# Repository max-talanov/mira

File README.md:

# MIRA

## Интерактивный атлас архитектуры 4.3

**[Скачать атлас ZIP](https://github.com/max-talanov/mira/raw/refs/heads/main/docs/architecture-atlas/MIRA_Architecture_Atlas_4.3.zip)** · **[Инструкция по запуску](docs/architecture-atlas/README.md)**

Скачайте и полностью распакуйте архив, затем откройте `MIRA_Architecture_Atlas/index.html` в Firefox или Chrome. Атлас работает локально: установка, сервер, интернет и KiCad для просмотра не нужны. Кнопка **«Презентация»** запускает обзор архитектуры; `guide.html` содержит текст для выступления.

Атлас 4.3 — отдельный демонстрационный снимок схем, подготовленный 22 октября 2026 года. Он не включает последующие исправления плат. Актуальные инженерные исходники находятся в [`hardware/`](hardware/).

## Обновления схем

**MIRA.06, 30 октября 2026:** [компоненты, разъёмы и сборка](docs/pcb-preparation/components-assembly/README.md). Уточнены 112 записей компонентов; исправлены SMT-footprint J100 и отверстия J600. BOM: 2148 обозначений / 322 группы; закупочные статусы и условия монтажа BGA/0201 записаны. Схемные соединения сохранены. Чертёж и открывание сокета, полный OPN входного клеммника, закупка, допуски и нагрузка разъёмов, подтверждение сборщика остаются открытыми; разрешения на производство нет.

**MIRA.05, 30 октября 2026:** [требования аналоговой части и исправления схемы](docs/pcb-preparation/analog-requirements/README.md). U2109 заменён на INA149AIDR с новой распиновкой; потолок команды снижен до 10,05 В, порог готовности P15 повышен до 13,22 В. Сохранены исправления пары CV 100/101 кОм и восьми записей BOM из промежуточного обновления; итоговая дельта — 12 компонентов. Заданы предварительные диапазоны READ/SET/RESET/FORMING, ток, нагрузка, одновременность и время; свойства реальной матрицы оставлены неизвестными. ERC 0 ошибок / 0 предупреждений на обеих платах. Пиковый ток, устойчивость, точность и время импульсов требуют отдельной проверки; прошивка и PCB не изменены.

**Решение от 30.10.2026: проверка MIG/Vivado отложена по согласованию с пользователем. Вернуться к ней перед трассировкой FPGA ↔ DDR3L на плате Control и до окончательной фиксации распиновки FPGA. По решению пользователя текущая карточка MIRA.04 закрывается как завершённый схемный этап; проверка MIG остаётся незавершённым условием перед трассировкой. Остальные проверки схемы, проектирование Power и независимые участки Control можно продолжать.**

**MIRA.04, 30 октября 2026:** [проверка цифровых интерфейсов](docs/pcb-preparation/digital-interfaces/README.md). SPI SCK перенесён AB12 → Y11; FMC/AF и 164 FPGA-порта сверены, ERC 0/0. MIG/Vivado ещё не запускались; кандидатные XDC и процедура запуска находятся в `fpga/digital-interfaces/`. Закрытие текущей карточки не означает выполнения проверки MIG; её нужно завершить до трассировки DDR3L.

**Предыдущий этап v6, 30 октября 2026:** [исправления сигналов при отключённом питании](docs/pcb-preparation/signal-remediation/README.md). Power — 61 лист / Control — 43; ERC 0/0. Закрытие — по схеме в указанных условиях; испытания платы и PCB открыты. AON: суммарный добавочный резерв 112 mA и 2.8 µF к бюджету 28 октября. Данные прежних этапов ниже сохранены как история.

**MIRA is a research platform under development for experiments with memristor arrays and neuromorphic computing.**

The project aims to bring array control, an analog front end, digital processing, and software tools into a single system. It is intended for studying memristor readout and programming, vector–matrix multiplication (VMM), and spiking neuron models.

## Current status

The current **MIRA.05 analog requirements** revision defines a provisional operating envelope and repairs the anti-windup amplifier, command ceiling and P15 qualifier. See the [analog report](docs/pcb-preparation/analog-requirements/README.md). Native ERC and historical regressions pass; matrix-specific limits, loop stability and transient peak-current qualification remain open.

The previous **2026-10-30 v6 signal remediation** adds hardware protection for PM, DAC, ADC/FDA and comparator inputs; replaces 33 analog switch ICs with fail-safe-input parts; isolates 10 VIN-relative enable paths; and qualifies USB and FPGA AUX/IO supplies. See the [current review and operating conditions](docs/pcb-preparation/signal-remediation/README.md). There are 271 new components and 40 changed legacy values. Native KiCad ERC reports zero errors and warnings. The checklist can be closed as a schematic review within those conditions. PCB, firmware and prototype qualification remain open. The [v5 receiver-only report](docs/pcb-preparation/unpowered-signals/README.md) is historical.

The preceding [fault hardware repair](docs/pcb-preparation/fault-review/README.md) adds a 170–230 ms application heartbeat watchdog, first-edge readiness and direct host reset on watchdog expiry. LINK_READY_H feeds the matrix interlock and PM PC15. The 14 added components are checked by native netlist and ideal timing/latch tests; firmware and prototype validation remain open.

The **2026-10-29** update adds [AON startup gating and full-swing VTT enable](docs/pcb-preparation/startup/README.md), plus [PM clear feedback and the 15-rail sequencing contract](docs/pcb-preparation/sequencing/README.md). The PM firmware must read GLOBAL_CLEAR_N on PC14 before arming, then confirm GLOBAL_PWR_PERMIT. Firmware implementation and prototype fault/ramp tests remain open.

**RevA** is currently in development. The repository contains two independent KiCad projects with local libraries: **MIRA_Control (43 active schematic pages)** and **MIRA_Power (61 active schematic pages)**.

Control includes MCU, FPGA, communications, matrix, analog, and protection circuits. Both projects are undergoing review before PCB placement and routing.

The [high-load schematic candidate](docs/pcb-preparation/high-load/README.md) dated **2026-10-28** adds a supplemental CORE connector and positive remote sense, replaces N15 with a TEN 30-2413WIN module, and coordinates N15 overcurrent and input overvoltage thresholds. The candidate input range is **18–30 V DC**, nominal 24 V. The provisional targets are CORE 5.2 A and N15 0.468 A; hardware capacity has not been validated.

The [distributed power interface](docs/pcb-preparation/distributed-power/README.md) replaces the central 64-contact connector with **seven local power entries and one separate supervision interface**. The zones are FPGA, DDR, MCU, USB, Ethernet, DAC/matrix and ADC/AFE. Eight Samtec SSW/HTSW pairs have assigned parts, local footprints and nominal 3D envelope models. The proposed stack has Power below Control and a 12 mm facing-surface gap; final placement coordinates and routing remain to be defined.

All 118 mating contacts were checked. The 6686-entry connector regression baseline from `c72edb2` remains matched after explicitly mapping back the documented startup, PC14 feedback, fault hardware the three v5 receive-path changes, and the explicit v6 signal-remediation delta; unrelated source/load circuits and positive CORE sense are preserved. The new pinout requires updating both projects together. The [earlier connector/ERC report](docs/pcb-preparation/connectors-erc/README.md) is retained as history.

KiCad CLI 10.0.8 reports **0 errors / 0 warnings / 0 exclusions for both projects**. Negative analog supply pins are now named VSS_NEG, with their power-input types and nets preserved; 32 old exclusions were removed. Two existing style checks remain ignored (`four_way_junction`, `single_global_label`); footprint-filter and simulation-model checks were re-enabled. PCB layout, mechanical and thermal qualification, feedback stability, startup and analog noise remain open. The [task 1/2 status and remaining questions](docs/pcb-preparation/README.md), [current ERC review](docs/pcb-preparation/erc/README.md) and [updated power budget](docs/pcb-preparation/power-budget/README.md) describe the current candidate. Original reports and calculations remain available as history. The budget applies a 30% margin to provisional peak loads and explicitly leaves N15 startup and shared-rail current distribution unresolved.

Schematics in this repository do not imply that the corresponding circuits have been built or validated in hardware.

## Repository contents

| Project | Current contents | Open in KiCad |
| --- | --- | --- |
| [MIRA_Power](hardware/MIRA_Power) | Power schematics, hierarchy, and local libraries | `hardware/MIRA_Power/MIRA_Power.kicad_pro` |
| [MIRA_Control](hardware/MIRA_Control) | 43-page schematic hierarchy, an empty PCB, and local symbol, footprint, and 3D libraries | `hardware/MIRA_Control/MIRA_Control.kicad_pro` |

Each project has its own library tables and project-relative library paths. Keep its complete folder together.

The power project includes:

| File or directory | Purpose |
| --- | --- |
| `MIRA_Power.kicad_pro` | KiCad project file |
| `MIRA_Power.kicad_sch` | Top-level schematic and hierarchy navigation |
| `POWER_SYSTEM.kicad_sch` | Power system overview |
| `POWER_INPUT.kicad_sch` | Power input and primary protection |
| `PRIMARY_POWER.kicad_sch` | Primary power converters |
| `SECONDARY_POWER.kicad_sch` | Secondary power converters |
| `PROGRAM_SWITCHES.kicad_sch` | Programming voltage switching |
| `POWER_CONTROL.kicad_sch` | Power control and protection interlocks |
| `POWER_MONITOR.kicad_sch` | Voltage and current monitoring |
| `libraries/` | Local symbol, footprint, and 3D model libraries |

The power system is designed around an external **24 V DC supply**. It provides digital and analog power rails, controlled startup, rail monitoring, and fault shutdown.

## Planned architecture

- **Memristor array and analog front end:** readout, programming, and VMM operations.
- **FPGA:** array timing control and high-speed data transfer.
- **STM32:** neuron model computation and control tasks.
- **USB 3.0 and Ethernet:** communication with a host computer.
- **Mira Studio:** a desktop application for configuring experiments, controlling the device, visualizing data, and saving results.

These blocks describe the planned development direction. Their implementation status is reflected in the current project files.

## Opening the projects

1. Clone the repository:

   ```bash
   git clone https://github.com/max-talanov/mira.git
   ```

2. Open the required `.kicad_pro` file from the table above. On Linux:

   ```bash
   cd mira
   kicad hardware/MIRA_Power/MIRA_Power.kicad_pro
   # Or open the control project:
   kicad hardware/MIRA_Control/MIRA_Control.kicad_pro
   ```

3. In both projects, use the schematic hierarchy to navigate between blocks. Open the root schematic through the project manager so the project-relative libraries are available.

Keep the directory structure intact. The `sym-lib-table` and `fp-lib-table` files are stored alongside the project and reference its local libraries.

## Versioning

**RevA** identifies the hardware revision. Git tags such as `v0.1.0` mark development milestones in the repository history.

| Tag | Milestone |
| --- | --- |
| `v0.1.0` | Initial KiCad project and local library import |
| `v0.2.0` | Separate Power and empty Control projects, with updated repository documentation |

Use commits for routine edits and annotated tags for milestones. Keep published tags on their original commits. A new repository tag does not change the hardware revision or indicate completed hardware validation.

See [CHANGELOG.md](CHANGELOG.md), the [commit history](https://github.com/max-talanov/mira/commits/main), and the [tag list](https://github.com/max-talanov/mira/tags).

## Licenses and attribution

See [LICENSE](LICENSE) and the third-party library and model notices included under each project's `libraries/` directory. Keep those notices with the corresponding assets.

## Next steps

- Establish the FPGA/matrix maximum operating scenario and recalculate the full power budget for the new N15 module.
- Co-design both PCB floorplans around the eight connector pairs; place regulators and local returns near their assigned load zones and qualify the proposed 12 mm mechanical stack.
- Validate CORE remote-sense stability, N15 startup/protection/noise and input surge response.
- Complete the remaining domain sequencing, reset/STOP and VTT/DDR_VREF reviews listed in the [candidate report](docs/pcb-preparation/high-load/README.md). The VSS ERC-exclusion review is resolved in the connector/ERC update.
- Prepare and review component placement and PCB routing before hardware validation.

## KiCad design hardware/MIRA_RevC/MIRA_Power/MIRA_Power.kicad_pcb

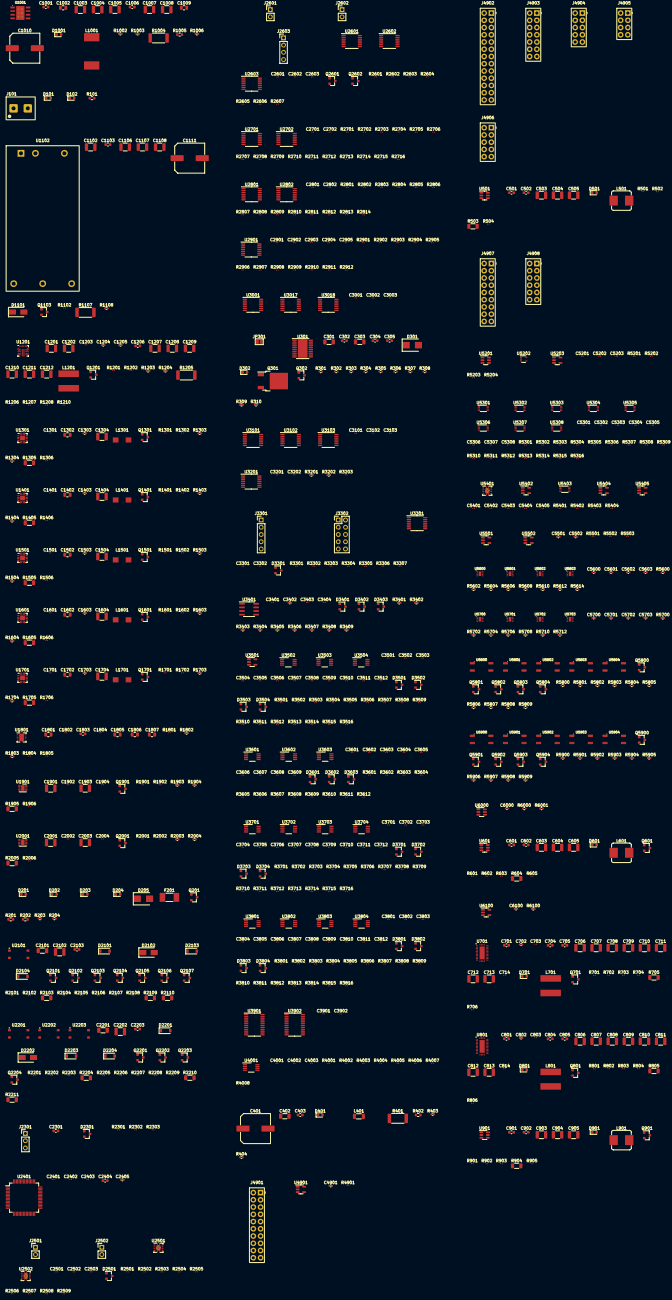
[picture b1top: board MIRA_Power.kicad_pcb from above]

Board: 4 copper layers, 793 parts (0 on the bottom side), 403 nets, no tracks yet.

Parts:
C301, C303, C402: 1u; C_1206_3216Metric
C302, C304, C305, C403, C501, C502, C601, C602, C705, C805, C901, C902, C1001, C1006, C1103, C2103, C2203, C2301: 100n; C_0603_1608Metric
C401, C1010, C1111: 100u; C_Elec_10x10.2
C503, C603, C706, C707, C806, C807, C903, C1003, C1008, C1102, C2102, C2202: 4.7u; C_1210_3225Metric
C504, C505, C604, C605, C708, C709, C710, C711, C712, C713, C808, C809, C810, C811, C812, C813, C904, C905, C1201, C1202, C1207, C1208, C1209, C1210, C1211, C1212, C1304, C1404, C1504, C1604, C1704, C1901, C1903, C2001, C2003: 47u; C_1210_3225Metric
C701, C801: 2.2u; C_0603_1608Metric
C702, C802, C2405: 1u; C_0402_1005Metric
C703, C803, C1203: 22n; C_0201_Murata_GRM03_Gap0.25
C704, C804: 470n; C_0603_1608Metric
C714, C814: 150p; C_0201_Murata_GRM03_Gap0.25
C1002: 220n; C_0805_2012Metric
C1004, C1005, C1007: 10u; C_1210_3225Metric
C1009: 1u; C_0805_2012Metric
C1106, C1107, C1108: 22u; C_1210_3225Metric
C1204, C1205, C1303, C1403, C1503, C1603, C1703, C3402, C4901, C5501, C5502, C5600, C5601, C5602, C5603, C5700, C5701, C5702, C5703, C6000, C6100: 100n; C_0402_1005Metric
C1206, C1803, C2404: 4.7u; C_0603_1608Metric
C1301, C1401, C1501, C1601, C1701, C1904, C2004, C2502, C2901, C2902, C2903, C2904, C3201, C3301, C3501, C3503, C3504, C3506, C3507, C3509, C3510, C3512, C3601, C3603, C3604, C3606, C3607, C3609, C3701, C3703, C3704, C3706, C3707, C3709, C3710, C3712, C3801, C3802, C3805, C3806, C3807, C3808, C3811, C3812: 10n; C_0201_Murata_GRM03_Gap0.25
C1302, C1402, C1502, C1602, C1702, C1801, C1805, C1806, C1807: 10u; C_0805_2012Metric
C1802, C1804, C1902, C2002, C2401, C2402, C2403, C2501, C2503, C2601, C2602, C2603, C2701, C2702, C2801, C2802, C2905, C3001, C3002, C3003, C3101, C3102, C3103, C3202, C3302, C3401, C3403, C3404, C3502, C3505, C3508, C3511, C3602, C3605, C3608, C3702, C3705, C3708, C3711, C3803, C3804, C3809, C3810, C3901, C3902, C4001, C5201, C5202, C5203, C5301, C5302, C5303, C5304, C5305, C5306, C5307, C5308, C5401, C5402, C5403, C5404, C5405: 100n; C_0201_Murata_GRM03_Gap0.25
C2101, C2201: 47n; C_1206_3216Metric
C4002, C4003: 1n; C_0201_Murata_GRM03_Gap0.25
D101, D202, D302: Red LED; LED_0603_1608Metric
D102, D204, D401, D501, D601, D701, D801, D901, D1001: Green LED; LED_0603_1608Metric
D201, D203: CD0603-B0240R; D_0603_1608Metric
D205: SMBJ36CA; D_SMB
D301: STPS3H100U; D_SMB
D1101: SS14-13-F; D_SMA
D2101, D2103, D2104, D2201, D2203, D2204: 10V G-S CLAMP; D_SOD-123
D2102, D2202: SS14 OUTPUT CLAMP; D_SMA
D2301: BAT54S ADC CLAMP; SOT-23
D2501: BAT54A; SOT-23
D3301, D3401, D3402, D3403, D3501, D3502, D3503, D3504, D3601, D3602, D3603, D3701, D3702, D3703, D3704, D3801, D3802, D3803, D3804: BAT54S; SOT-23
F201: 5A / 125V; Fuse_Littelfuse_0451_2410_Mfr
J101: DG126-5.0-02P-14; TerminalBlock_Degson_DG126-5.0-02P-14_1x02_P5.00mm
J2301: PROGRAM +/-15V; PinHeader_1x03_P2.54mm_Vertical
J2501: PM MANUAL RESET CONTACT; PinHeader_1x02_P2.54mm_Vertical
J2502: HOST MANUAL RESET CONTACT; PinHeader_1x02_P2.54mm_Vertical
J2601: GLOBAL STOP - CLOSE TO TRIP; PinHeader_1x02_P2.54mm_Vertical
J2602: MATRIX STOP - CLOSE TO TRIP; PinHeader_1x02_P2.54mm_Vertical
J2603: MATRIX HARDWARE INTERLOCK - AON LOGIC; PinHeader_1x04_P2.54mm_Vertical
J3301: PM SWD - VTREF ONLY; PinHeader_1x05_P2.54mm_Vertical
J3302: MAIN CONTROLLER UART / WATCHDOG / STATUS; PinHeader_2x05_P2.54mm_Vertical
J4901: SSW-110-01-S-D; Samtec_SSW-110-01-S-D_2x10_P2.54mm_Vertical
J4902: SSW-113-01-S-D; Samtec_SSW-113-01-S-D_2x13_P2.54mm_Vertical
J4903: SSW-107-01-S-D; Samtec_SSW-107-01-S-D_2x07_P2.54mm_Vertical
J4904, J4906: SSW-105-01-S-D; Samtec_SSW-105-01-S-D_2x05_P2.54mm_Vertical
J4905: SSW-104-01-S-D; Samtec_SSW-104-01-S-D_2x04_P2.54mm_Vertical
J4907: SSW-109-01-S-D; Samtec_SSW-109-01-S-D_2x09_P2.54mm_Vertical
J4908: SSW-106-01-S-D; Samtec_SSW-106-01-S-D_2x06_P2.54mm_Vertical
JP301: SolderJumper_2_Open; SolderJumper-2_P1.3mm_Open_Pad1.0x1.5mm
L401: 120R @ 100MHz / 6A; L_1206_3216Metric
L501, L601, L901: 33uH; L_Bourns_SRP7028A_7.3x6.6mm
L701, L801: 6.8uH; L_Bourns_SRP7030CA_7.8x7.6mm
L1001: 47u; L_Wurth_7447709101_12x12mm
L1201: 1u; L_Bourns_SRP7030CA_7.8x7.6mm
L1301, L1401, L1501, L1601, L1701: 2.2u; L_Bourns_SRP5030TA_5.7x5.2mm
Q201, Q302, Q601, Q701, Q801, Q901, Q1103, Q1201, Q1301, Q1401, Q1501, Q1601, Q1701, Q1901, Q2001, Q2601, Q2602: BSS138N; SOT-23
Q301: IRFR3410; TO-252-2
Q2101, Q2104, Q2106, Q2107, Q2201, Q2202, Q2203, Q5800, Q5801, Q5802, Q5803, Q5804, Q5900, Q5901, Q5902, Q5903, Q5904: AO3400A; SOT-23
Q2102, Q2103, Q2105, Q2204: AO3401A; SOT-23
R101, R201, R202, R402, R1005: 10k; R_0603_1608Metric
R203, R5801, R5803, R5805, R5807, R5809, R5901, R5903, R5905, R5907, R5909: 22k; R_0402_1005Metric
R204, R306, R307, R3407, R3408, R3409: 10k; R_0402_1005Metric
R301: 12.1k; R_0402_1005Metric
R302: 16.2k; R_0402_1005Metric
R303, R304: 180k; R_0402_1005Metric
R305: 4.02k; R_0402_1005Metric
R308: 24k; R_0402_1005Metric
R309, R310: 150k; R_0402_1005Metric
R401: 20m / 1W; R_2512_6332Metric
R403, R404, R1002, R1006, R1108, R3402, R5600, R5602, R5604, R5606, R5608, R5610, R5612, R5614, R5700, R5702, R5704, R5706, R5708, R5710, R5712, R6000, R6100: 100k; R_0402_1005Metric
R501: 62k; R_0201_Panasonic_ERJ1G_Gap0.30
R502, R603, R903: 20k; R_0201_Panasonic_ERJ1G_Gap0.30
R503: 0.1R; R_1206_3216Metric
R504, R605, R706, R806, R905, R3304, R3305, R3504, R3508, R3512, R3516, R3604, R3608, R3612, R3704, R3708, R3712, R3716, R3807, R3808, R3815, R3816: 1k; R_0201_Panasonic_ERJ1G_Gap0.30
R601, R702, R703, R802, R803, R901, R1102, R1201, R1301, R1401, R1501, R1601, R1701, R1801, R1901, R2001, R2104, R2106, R2107, R2108, R2205, R2207, R2209, R2502, R2507, R2601, R2604, R2606, R2607, R2701, R2702, R2703, R2704, R2705, R2706, R2707, R2708, R2709, R2710, R2711, R2712, R2713, R2714, R2715, R2716, R2801, R2802, R2803, R2804, R2805, R2806, R2807, R2808, R2809, R2810, R2811, R2812, R2813, R2814, R3303, R3306, R3307, R4001, R4002, R4003, R4004, R4007, R4901, R5202, R5204, R5404, R5501, R5502, R5503: 100k; R_0201_Panasonic_ERJ1G_Gap0.30
R602: 105k; R_0201_Panasonic_ERJ1G_Gap0.30
R604, R904, R1905, R2005: 0.05R; R_1206_3216Metric
R701, R801, R1202, R1206, R1208, R1302, R1306, R1402, R1406, R1502, R1506, R1602, R1606, R1702, R1706, R1804, R1902, R1906, R2002, R2006, R2302, R2303, R2501, R2503, R2504, R2505, R2506, R2508, R2509, R2602, R2603, R2605, R2905, R2906, R2907, R2908, R2909, R2910, R2911, R2912, R3203, R3503, R3505, R3506, R3507, R3509, R3510, R3511, R3513, R3514, R3515, R3601, R3602, R3603, R3605, R3606, R3607, R3610, R3701, R3702, R3705, R3706, R3707, R3709, R3710, R3711, R3713, R3714, R3715, R3801, R3802, R3803, R3804, R3806, R3809, R3810, R3811, R3812, R3813, R3814, R4008, R5313, R5316, R5401, R5402, R5403: 10k; R_0201_Panasonic_ERJ1G_Gap0.30
R704: 43.2k; R_0201_Panasonic_ERJ1G_Gap0.30
R705, R805, R1605: 0.01R; R_1206_3216Metric
R804: 22.1k; R_0201_Panasonic_ERJ1G_Gap0.30
R902: 130k; R_0201_Panasonic_ERJ1G_Gap0.30
R1003: 7.15k; R_0402_1005Metric
R1004, R1107: 0.1R; R_2512_6332Metric
R1203: 10.2k; R_0402_1005Metric
R1204: 15.0k; R_0402_1005Metric
R1205: 0.002R; R_2512_6332Metric
R1207: 200k; R_0201_Panasonic_ERJ1G_Gap0.30
R1210, R4005, R4006: 100; R_0201_Panasonic_ERJ1G_Gap0.30
R1303: 20.0k; R_0402_1005Metric
R1304, R1404, R1504, R1604, R1704, R2004: 16.0k; R_0402_1005Metric
R1305, R1405, R1505, R1705: 0.02R; R_1206_3216Metric
R1403: 34.0k; R_0402_1005Metric
R1503, R2003: 49.9k; R_0402_1005Metric
R1603: 11.0k; R_0402_1005Metric
R1703: 20k; R_0402_1005Metric
R1802, R1803, R3202, R3401, R3403, R3406: 10.0k; R_0402_1005Metric
R1805: 0R; R_0201_Panasonic_ERJ1G_Gap0.30
R1903: 10.5k; R_0402_1005Metric
R1904: 2.00k; R_0402_1005Metric
R2101, R2203: 330k; R_0201_Panasonic_ERJ1G_Gap0.30
R2102, R2202: 1M; R_0201_Panasonic_ERJ1G_Gap0.30
R2103, R2109, R2110, R2204, R2210, R2211: 680R; R_1206_3216Metric
R2105, R2201, R2206, R2208: 300; R_0201_Panasonic_ERJ1G_Gap0.30
R2301, R3609, R5306: 47k; R_0201_Panasonic_ERJ1G_Gap0.30
R2901: 4.7k; R_0201_Panasonic_ERJ1G_Gap0.30
R2902: 2.2k; R_0201_Panasonic_ERJ1G_Gap0.30
R2903: 3.9k; R_0201_Panasonic_ERJ1G_Gap0.30
R2904: 15k; R_0201_Panasonic_ERJ1G_Gap0.30
R3201: 2.74k; R_0402_1005Metric
R3301, R3302: 33; R_0201_Panasonic_ERJ1G_Gap0.30
R3404, R3405: 200k; R_0402_1005Metric
R3501, R3502: 75k; R_0201_Panasonic_ERJ1G_Gap0.30
R3611: 30.1k; R_0201_Panasonic_ERJ1G_Gap0.30
R3703: 7.50k; R_0201_Panasonic_ERJ1G_Gap0.30
R3805: 13.7k; R_0201_Panasonic_ERJ1G_Gap0.30
R5201: 590k; R_0201_Panasonic_ERJ1G_Gap0.30
R5203: 150k; R_0201_Panasonic_ERJ1G_Gap0.30
R5301, R5302, R5303, R5304, R5305, R5307, R5308, R5309, R5310, R5311, R5312, R5314, R5315: 220k; R_0201_Panasonic_ERJ1G_Gap0.30
R5800, R5802, R5804, R5806, R5808, R5900, R5902, R5904, R5906, R5908: 270; R_0402_1005Metric
R6001: 1k; R_0402_1005Metric
U301: TPS26631PWPR; HTSSOP-20-1EP_4.4x6.5mm_P0.65mm_EP3.4x6.5mm_Mask2.96x2.96mm
U501, U601, U901: LMR51610XDBVR; SOT-23-6
U701, U801: LM76005RNPR; TI_LM76005_RNP0030G
U1001: LMR36520FADDAR; TI_DDA0008B
U1102: ECB40W18-72S15N; Cincon_ECB40W18_no_bus
U1201: TPS568215RNNR; Texas_RNN0018A
U1301, U1401, U1501, U1601, U1701: TPS62130ARGTR; VQFN-16-1EP_3x3mm_P0.5mm_EP1.68x1.68mm
U1801: TPS51200DRCR; Texas_DRC0010J
U1901, U2001: TPS7A9101DSKR; WSON-10-1EP_2.5x2.5mm_P0.5mm_EP1.2x2mm
U2101, U2201, U2202, U2203: LTV-356T-A; LTV356T_SOP4_P2.54mm_Mfr
U2401: STM32G0B1RBT6; LQFP-64_10x10mm_P0.5mm
U2501, U2502, U5401: TPS3851H33EDRBR; Texas_DRB0008A
U2601, U2602, U3001, U3017, U3018, U3101, U3102, U3103: SN74HCS21PWR; TSSOP-14_4.4x5mm_P0.65mm
U2603: SN74HC74PWR; TSSOP-14_4.4x5mm_P0.65mm
U2701, U2702, U2801, U2802: SN74HC08PWR; TSSOP-14_4.4x5mm_P0.65mm
U2901, U3201: TLV1704AIPWR; TSSOP-14_4.4x5mm_P0.65mm
U3301: 74LVC125APW,118; TSSOP-14_4.4x5mm_P0.65mm
U3401: OPA2991IDR; SOIC-8_3.9x4.9mm_P1.27mm
U3501: INA293A1IDBVR; SOT-23-5
U3502, U3503, U3504, U3601, U3602, U3603, U3702, U3703, U3704, U3802, U3803, U3804: INA301A1IDGKR; VSSOP-8_3.0x3.0mm_P0.65mm
U3701, U3801: INA301A2IDGKR; VSSOP-8_3.0x3.0mm_P0.65mm
U3901, U3902: CD74HC4067PWR; TSSOP-24_4.4x7.8mm_P0.65mm
U4001: TLV9002IDGKR; VSSOP-8_3.0x3.0mm_P0.65mm
U4901, U5501, U5502, U6100: 74LVC1G17GV,125; SOT-23-5
U5201: TPS3808G01DBVR; SOT-23-6
U5202: 74AUP1G34GW; SOT-353_SC-70-5
U5203, U5404: 74LVC1G08GV; SOT-23-5
U5301, U5302, U5303, U5304, U5305, U5306, U5307, U5308: 74AUP2G126DC; VSSOP-8_2.3x2mm_P0.5mm
U5402: 74LVC1G14GV; SOT-23-5
U5403: SN74LVC1G74DCUR; VSSOP-8_2.3x2mm_P0.5mm
U5405: SN74LVC1G07DBVR; SOT-23-5
U5600, U5601, U5602, U5603, U5700, U5701, U5702, U5703: TMUX2821DSGR; WSON-8_2x2mm_P0.5mm_EP0.9x1.6mm
U5800, U5801, U5802, U5803, U5804, U5900, U5901, U5902, U5903, U5904: TLP172GM(TPR,E); SO6_4Pin_Toshiba_11-4M1S
U6000: SN74LVC1G11; SOT-23-6

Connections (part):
+24V_FUSED: C301.1, C302.2, D205.2 (A2), F201.2, Q301.3 (S), Q302.2 (S), R202.2, R203.1, R304.2, U301.6 (IN_SYS)
+24V_RAW: F201.1, J101.1, R101.2, R201.1
/POWER_SYSTEM/POWER_CONTROL/2600_PM_PERMIT_INTERLOCKS/INPUT_AON_OK: U2601.6 (1Y), U2601.9 (2A)
/POWER_SYSTEM/POWER_CONTROL/2600_PM_PERMIT_INTERLOCKS/MATRIX_BASE_OK: U2602.6 (1Y), U2602.9 (2A)
/POWER_SYSTEM/POWER_CONTROL/2600_PM_PERMIT_INTERLOCKS/MATRIX_CLEAR_N: U2602.8 (2Y), U2603.13 (2CLR_N)
/POWER_SYSTEM/POWER_CONTROL/3000_PM_RAIL_READY/PG_GROUP_0: U3001.6 (1Y), U3018.1 (1A)
/POWER_SYSTEM/POWER_CONTROL/3000_PM_RAIL_READY/PG_GROUP_1: U3001.8 (2Y), U3018.2 (1B)
/POWER_SYSTEM/POWER_CONTROL/3000_PM_RAIL_READY/PG_GROUP_2: U3017.6 (1Y), U3018.4 (1C)
/POWER_SYSTEM/POWER_CONTROL/3000_PM_RAIL_READY/PG_GROUP_3: U3017.8 (2Y), U3018.5 (1D)
/POWER_SYSTEM/POWER_CONTROL/3100_PM_COMMAND_READY/CMD_GROUP_0: U3101.6 (1Y), U3103.1 (1A)
/POWER_SYSTEM/POWER_CONTROL/3100_PM_COMMAND_READY/CMD_GROUP_1: U3101.8 (2Y), U3103.2 (1B)
/POWER_SYSTEM/POWER_CONTROL/3100_PM_COMMAND_READY/CMD_GROUP_2: U3102.6 (1Y), U3103.4 (1C)
/POWER_SYSTEM/POWER_CONTROL/3100_PM_COMMAND_READY/CMD_GROUP_3: U3102.8 (2Y), U3103.5 (1D)
ADC_I: C4002.2, R4005.2, U2401.17 (PA0)
ADC_V: C4003.1, R4006.2, U2401.18 (PA1)
ADC_VTT: C3301.1, R3304.2, U5703.1 (S1)
ADC_VTT_SAFE: D3301.3 (K1/A2), R5712.1, U2401.19 (PA2), U5703.2 (D1)
ALL_COMMANDS_ON: U2602.4 (1C), U3103.6 (1Y)
ALL_RAILS_PG: U2401.3 (PC13), U2602.2 (1B), U3018.6 (1Y), U3301.9 (3A)
ALL_RAILS_PG_POWER: J3302.7, J4901.9, U3301.8 (3Y)
ANA3V3: J4908.7, R2005.2, R2006.1, R3811.2, U3804.7 (IN-)
ANA5: C2001.1, J4907.9, J4908.5, Q2001.3 (D), R1905.2, R1906.1, R3803.2, U2001.9 (IN), U2001.10 (IN), U3802.7 (IN-)
ANA5_RAW: C1903.1, C1904.1, R1903.1, R1905.1, U1901.1 (OUT), U1901.2 (OUT), U3802.8 (IN+)
ANA6: C1901.1, Q1901.3 (D), R904.2, R905.1, R3605.2, U1901.9 (IN), U1901.10 (IN), U3602.7 (IN-)
ANA33_RAW: C2003.1, C2004.1, R2003.1, R2005.1, U2001.1 (OUT), U2001.2 (OUT), U3804.8 (IN+)
ANA_CB: C902.1, U901.1 (CB)
ANA_FB: R902.1, R903.2, U901.3 (FB)
ANA_RAW: C904.2, C905.2, L901.2, R902.2, R904.1, U3602.8 (IN+)
ANA_SW: C902.2, L901.1, U901.6 (SW)
AON: C1803.1, C2401.1, C2402.1, C2403.1, C2404.1, C2405.1, C2501.1, C2601.1, C2602.1, C2603.1, C2701.1, C2702.1, C2801.1, C2802.1, C2905.1, C3001.1, C3002.1, C3003.1, C3101.1, C3102.1, C3103.1, C3202.1, C3401.1, C3502.1, C3505.1, C3508.1, C3511.1, C3602.1, C3605.1, C3608.1, C3702.1, C3705.1, C3708.1, C3711.1, C3803.1, C3804.1, C3809.1, C3810.1, C3901.1, C3902.1, C4001.1, C4901.1, C5201.1, C5202.1, C5203.1, C5301.1, C5302.1, C5303.1, C5304.1, C5305.1, C5306.1, C5307.1, C5308.1, C5401.1, C5402.1, C5403.1, C5404.1, C5405.1, C5501.1, C5502.1, C5600.1, C5601.1, C5602.1, C5603.1, C5700.1, C5701.1, C5702.1, C5703.1, C6000.1, C6100.1, D2301.2 (K), D3301.2 (K), D3401.2 (K), D3402.2 (K), D3403.2 (K), D3501.2 (K), D3502.2 (K), D3503.2 (K), D3504.2 (K), D3601.2 (K), D3602.2 (K)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
AON_CB: C502.1, U501.1 (CB)
AON_FB: R501.1, R502.2, U501.3 (FB)
AON_MON_ENABLE: R6100.1, U5600.3 (SEL2), U5600.7 (SEL1), U5601.3 (SEL2), U5601.7 (SEL1), U5602.3 (SEL2), U5602.7 (SEL1), U5603.3 (SEL2), U5603.7 (SEL1), U5700.3 (SEL2), U5700.7 (SEL1), U5701.3 (SEL2), U5701.7 (SEL1), U5702.3 (SEL2), U5702.7 (SEL1), U5703.7 (SEL1), U6100.4 (Y)
AON_RAW: C504.2, C505.2, L501.2, R501.2, R503.1, U3502.8 (IN+)
AON_RESET_N: D2501.1 (K1), R2504.1, U2501.8 (RESET_N), U2601.1 (1A)
AON_SW: C502.2, L501.1, U501.6 (SW)
AUX1V8: J4902.19, J4902.21, R1305.2, R1306.1, R3705.2, U3702.7 (IN-)
AUX2V5: R1405.2, R1406.1, R3709.2, U3703.7 (IN-)
AUX18_RAW: C1304.1, L1301.2, R1303.1, R1305.1, U1301.7 (FSW), U1301.14 (VOS), U3702.8 (IN+)
AUX25_RAW: C1404.1, L1401.2, R1403.1, R1405.1, U1401.7 (FSW), U1401.14 (VOS), U3703.8 (IN+)
BUS24: C501.1, C503.1, C601.1, C603.1, C705.2, C706.2, C707.2, C805.2, C806.2, C807.2, C901.1, C903.1, C1002.1, C1003.1, C1008.1, C1102.1, C1103.1, C1111.1, Q601.3 (D), Q701.3 (D), Q801.3 (D), Q901.3 (D), R401.2, R402.2, R403.2, R3501.2, U501.4 (EN), U501.5 (VIN), U601.5 (VIN), U701.20 (PVIN), U701.21 (PVIN), U701.22 (PVIN), U801.20 (PVIN), U801.21 (PVIN), U801.22 (PVIN), U901.5 (VIN), U1001.2 (VIN), U1102.1 (+VIN), U3501.4 (IN-), U5800.6 (SW1), U5801.6 (SW1), U5802.6 (SW1), U5803.6 (SW1), U5804.6 (SW1)
BUS24_PRE_SHUNT: C401.1, C402.2, C403.2, L401.2, R401.1, U3501.3 (IN+)
CB_P15: C1001.1, U1001.7 (BOOT)
CMD_ANA: Q901.1 (G), R5304.1, U3101.5 (1D), U5302.3 (2Y)
CMD_ANA5: Q1901.1 (G), R5314.1, U3102.10 (2B), U5307.3 (2Y)
CMD_ANA5_RAW: R2813.1, U2802.6 (2Y), U5307.5 (2A)
CMD_ANA33: Q2001.1 (G), R5315.1, U3102.12 (2C), U5308.6 (1Y)
CMD_ANA33_RAW: R2814.1, U2802.8 (3Y), U5308.2 (1A)
CMD_ANA_RAW: R2708.2, U2701.11 (4Y), U5302.5 (2A)
CMD_AUX18: Q1301.1 (G), R5308.1, U3101.13 (2D), U5304.3 (2Y)
CMD_AUX18_RAW: R2716.2, U2702.11 (4Y), U5304.5 (2A)
CMD_AUX25: Q1401.1 (G), R5309.1, U3102.1 (1A), U5305.6 (1Y)
CMD_AUX25_RAW: R2805.1, U2801.3 (1Y), U5305.2 (1A)
CMD_CORE: Q1201.1 (G), R5307.1, U3101.12 (2C), U5304.6 (1Y)
CMD_CORE_RAW: R2715.1, U2702.8 (3Y), U5304.2 (1A)
CMD_DDR: Q1601.1 (G), R5311.1, U3102.4 (1C), U5306.6 (1Y)
CMD_DDR_RAW: R2807.1, U2801.8 (3Y), U5306.2 (1A)
CMD_FPGA: Q801.1 (G), R5303.1, U3101.4 (1C), U5302.6 (1Y)
CMD_FPGA_RAW: R2707.1, U2701.8 (3Y), U5302.2 (1A)
CMD_IO18: Q1701.1 (G), R5312.1, U3102.5 (1D), U5306.3 (2Y)
CMD_IO18_RAW: R2808.2, U2801.11 (4Y), U5306.5 (2A)
CMD_IO33: Q1501.1 (G), R5310.1, U3102.2 (1B), U5305.3 (2Y)
CMD_IO33_RAW: R2806.1, U2801.6 (2Y), U5305.5 (2A)
CMD_N15: Q1103.1 (G), R1102.1, R5306.1, U3101.10 (2B), U5303.3 (2Y)
CMD_N15_RAW: R2714.1, U2702.6 (2Y), U5303.5 (2A)
CMD_P15: Q5804.1 (G), R5305.1, U3101.9 (2A), U5303.6 (1Y)
CMD_P15_RAW: R2713.1, U2702.3 (1Y), U5303.2 (1A)
CMD_SYS: Q701.1 (G), R5302.1, U3101.1 (1A), U3101.2 (1B), U5301.3 (2Y)
CMD_SYS_RAW: R2706.1, U2701.6 (2Y), U5301.5 (2A)
CMD_USB: Q601.1 (G), R5301.1, U5301.6 (1Y)
CMD_USB_RAW: R2705.1, U2701.3 (1Y), U5301.2 (1A)
CMD_VTT: R1805.1, R5313.1, U3102.9 (2A), U5307.6 (1Y)
CMD_VTT_RAW: R2812.1, U2802.3 (1Y), U5307.2 (1A)
CORE1V0: J4902.1, J4902.3, J4902.5, J4902.7, J4902.9, J4902.11, J4902.13, J4902.15, R1205.2, R1206.1, R3701.2, U3701.7 (IN-)
CORE_RAW: C1207.2, C1208.1, C1209.2, C1210.1, C1211.2, C1212.1, L1201.2, R1205.1, R1210.1, U3701.8 (IN+)
CORE_SENSE_P: J4902.17, R1203.1, R1210.2
DDR1V35: C1801.1, J4903.1, J4903.3, J4903.5, R1605.2, R1606.1, R1803.1, R3801.2, U1801.2 (VLDOIN), U3801.7 (IN-)
DDR_RAW: C1604.1, L1601.2, R1603.1, R1605.1, U1601.7 (FSW), U1601.14 (VOS), U3801.8 (IN+)
DDR_VREF: C1804.1, J4903.11, U1801.6 (REFOUT)
EFUSE_OUT: C305.2, D301.1 (K), L401.1, R310.1, U301.18 (OUT), U301.19 (OUT), U301.20 (OUT)
EFUSE_OVP: R301.2, R302.1, U301.8 (OVP)
EFUSE_UVLO: R302.2, R303.1, U301.7 (UVLO)
EN_ANA: Q901.2 (S), Q5803.1 (G), R901.2
EN_ANA5: Q1901.2 (S), R1901.1, U1901.7 (EN)
EN_ANA33: Q2001.2 (S), R2001.1, U2001.7 (EN)
EN_ANA_LED_A: R5806.2, U5803.1 (A)
EN_ANA_LED_K: Q5803.3 (D), U5803.3 (K)
EN_ANA_VIN: R5807.1, U901.4 (EN), U5803.4 (SW2)
EN_AUX18: Q1301.2 (S), Q5900.1 (G), R1301.1, U6000.6 (C)
EN_AUX18_LED_A: R5900.2, U5900.1 (A)
EN_AUX18_LED_K: Q5900.3 (D), U5900.3 (K)
EN_AUX18_VIN: R5901.1, U1301.13 (EN), U5900.4 (SW2)
EN_AUX25: Q1401.2 (S), Q5901.1 (G), R1401.1
EN_AUX25_LED_A: R5902.2, U5901.1 (A)
EN_AUX25_LED_K: Q5901.3 (D), U5901.3 (K)
EN_AUX25_VIN: R5903.1, U1401.13 (EN), U5901.4 (SW2)
EN_CORE: Q1201.2 (S), R1201.1, U1201.15 (EN)
EN_DDR: Q1601.2 (S), Q5903.1 (G), R1601.1
EN_DDR_LED_A: R5906.2, U5903.1 (A)
EN_DDR_LED_K: Q5903.3 (D), U5903.3 (K)
EN_DDR_VIN: R5907.1, U1601.13 (EN), U5903.4 (SW2)
EN_FPGA: Q801.2 (S), Q5802.1 (G), R802.2
EN_FPGA_LED_A: R5804.2, U5802.1 (A)
EN_FPGA_LED_K: Q5802.3 (D), U5802.3 (K)
EN_FPGA_VIN: R5805.1, U801.18 (EN), U5802.4 (SW2)
EN_IO18: Q1701.2 (S), Q5904.1 (G), R1701.1
EN_IO18_LED_A: R5908.2, U5904.1 (A)
EN_IO18_LED_K: Q5904.3 (D), U5904.3 (K)
EN_IO18_VIN: R5909.1, U1701.13 (EN), U5904.4 (SW2)
EN_IO33: Q1501.2 (S), R1501.1, U6000.1 (A)
EN_IO33_LED_A: R5904.2, U5902.1 (A)
EN_IO33_LED_K: Q5902.3 (D), U5902.3 (K)
EN_IO33_QUAL: Q5902.1 (G), R6000.1, U6000.4 (Y)
EN_IO33_VIN: R5905.1, U1501.13 (EN), U5902.4 (SW2)
EN_P15_LED_A: R5808.2, U5804.1 (A)
EN_P15_LED_K: Q5804.3 (D), U5804.3 (K)
EN_P15_VIN: R5809.1, U1001.3 (EN), U5804.4 (SW2)
EN_REQ_ANA: R2701.2, U2401.23 (PA6), U2701.13 (4B)
EN_REQ_ANA5: R2810.1, U2401.33 (PB13), U2802.5 (2B)
EN_REQ_ANA33: R2811.1, U2401.34 (PB14), U2802.10 (3B)
EN_REQ_AUX18: R2709.2, U2401.27 (PB0), U2702.13 (4B)
EN_REQ_AUX25: R2802.1, U2401.28 (PB1), U2801.2 (1B)
EN_REQ_CORE: R2712.1, U2401.26 (PC5), U2702.10 (3B)
EN_REQ_DDR: R2804.1, U2401.30 (PB10), U2801.10 (3B)
EN_REQ_FPGA: R2704.1, U2401.22 (PA5), U2701.10 (3B)
EN_REQ_IO18: R2801.2, U2401.31 (PB11), U2801.13 (4B)
EN_REQ_IO33: R2803.1, U2401.29 (PB2), U2801.5 (2B)
EN_REQ_N15: R2711.1, U2401.25 (PC4), U2702.5 (2B)
EN_REQ_P15: R2710.1, U2401.24 (PA7), U2702.2 (1B)
EN_REQ_SYS: R2703.1, U2401.21 (PA4), U2701.5 (2B)
EN_REQ_USB: R2702.1, U2401.10 (PF0), U2701.2 (1B)
EN_REQ_VTT: R2809.1, U2401.32 (PB12), U2802.2 (1B)
EN_SYS: Q701.2 (S), Q5801.1 (G), R702.2
EN_SYS_LED_A: R5802.2, U5801.1 (A)
EN_SYS_LED_K: Q5801.3 (D), U5801.3 (K)
EN_SYS_VIN: R5803.1, U701.18 (EN), U5801.4 (SW2)
EN_USB: Q601.2 (S), Q5800.1 (G), R601.2
EN_USB_LED_A: R5800.2, U5800.1 (A)
EN_USB_LED_K: Q5800.3 (D), U5800.3 (K)
EN_USB_VIN: R5801.1, U601.4 (EN), U5800.4 (SW2)
EN_VTT: R1801.1, R1805.2, U1801.7 (EN)
FB_ANA5: C1904.2, R1903.2, R1904.1, U1901.3 (FB)
FB_ANA33: C2004.2, R2003.2, R2004.1, U2001.3 (FB)
FB_AUX18: R1303.2, R1304.1, U1301.5 (FB)
FB_AUX25: R1403.2, R1404.1, U1401.5 (FB)
FB_CORE: R1203.2, R1204.1, U1201.13 (FB)
FB_DDR: R1603.2, R1604.1, U1601.5 (FB)
FB_IO18: R1703.2, R1704.1, U1701.5 (FB)
FB_IO33: R1503.2, R1504.1, U1501.5 (FB)
FB_P15: R1002.2, R1003.1, U1001.5 (FB)
FLT_INPUT_N: D302.1 (K), R2603.1, U301.15 (FLT_N), U2401.43 (PA11), U2601.5 (1D)
FPGA5V5: C1201.1, C1202.2, C1204.1, C1302.1, C1303.1, C1402.1, C1403.1, C1502.1, C1503.1, C1602.1, C1603.1, C1702.1, C1703.1, Q1201.3 (D), Q1301.3 (D), Q1401.3 (D), Q1501.3 (D), Q1601.3 (D), Q1701.3 (D), R805.2, R806.1, R3601.2, U1201.2 (VIN), U1201.11 (VIN), U1301.10 (AVIN), U1301.11 (PVIN), U1301.12 (PVIN), U1401.10 (AVIN), U1401.11 (PVIN), U1401.12 (PVIN), U1501.10 (AVIN), U1501.11 (PVIN), U1501.12 (PVIN), U1601.10 (AVIN), U1601.11 (PVIN), U1601.12 (PVIN), U1701.10 (AVIN), U1701.11 (PVIN), U1701.12 (PVIN), U3601.7 (IN-), U5900.6 (SW1), U5901.6 (SW1), U5902.6 (SW1), U5903.6 (SW1), U5904.6 (SW1)
FPGA_BOOT: C804.1, U801.6 (BOOT)
FPGA_FB: C814.1, R803.1, R804.2, U801.12 (FB)
FPGA_RAW: C802.2, C808.2, C809.2, C810.2, C811.2, C812.2, C813.2, C814.2, L801.2, R803.2, R805.1, U801.9 (BIAS), U3601.8 (IN+)
FPGA_SS: C803.2, U801.11 (SS/TRK)
FPGA_SW: C804.2, L801.1, U801.1 (SW), U801.2 (SW), U801.3 (SW), U801.4 (SW), U801.5 (SW)
FPGA_VCC: C801.2, U801.8 (VCC)
GLOBAL_CLEAR_N: U2401.4 (PC14), U2603.1 (1CLR_N), U5203.4 (Y)
GLOBAL_CLEAR_RAW_N: U2601.8 (2Y), U5203.1 (A)
GLOBAL_PWR_PERMIT: U2401.47 (PA15), U2602.1 (1A), U2603.5 (1Q), U2701.1 (1A), U2701.4 (2A), U2701.9 (3A), U2701.12 (4A), U2702.1 (1A), U2702.4 (2A), U2702.9 (3A), U2702.12 (4A), U2801.1 (1A), U2801.4 (2A), U2801.9 (3A), U2801.12 (4A), U2802.1 (1A), U2802.4 (2A), U2802.9 (3A), U3301.12 (4A)
GLOBAL_PWR_PERMIT_POWER: J3302.8, J4901.11, U3301.11 (4Y)
GND: C301.2, C302.1, C303.2, C304.2, C305.1, C401.2, C402.1, C403.1, C501.2, C503.2, C504.1, C505.1, C601.2, C603.2, C604.1, C605.1, C701.1, C702.1, C703.1, C705.1, C706.1, C707.1, C708.1, C709.1, C710.1, C711.1, C712.1, C713.1, C801.1, C802.1, C803.1, C805.1, C806.1, C807.1, C808.1, C809.1, C810.1, C811.1, C812.1, C813.1, C901.2, C903.2, C904.1, C905.1, C1002.2, C1003.2, C1004.2, C1005.2, C1006.2, C1007.2, C1008.2, C1009.2, C1010.2, C1102.2, C1103.2, C1106.1, C1107.1, C1108.1, C1111.2, C1201.2, C1202.1, C1203.2, C1204.2, C1206.2, C1207.1, C1208.2, C1209.1, C1210.2, C1211.1, C1212.2, C1301.2, C1302.2, C1303.2, C1304.2, C1401.2, C1402.2, C1403.2, C1404.2, C1501.2, C1502.2, C1503.2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
HOST_ALIVE: J4901.3, R4901.1, U4901.2 (A)
HOST_ALIVE_PM: U2401.11 (PF1), U4901.4 (Y), U5401.6 (WDI), U5402.2 (A)
HOST_RESET_AON_N: R5502.1, U2602.10 (2B), U5501.4 (Y)
HOST_RESET_N: J4901.15, R2509.1, R5501.1, U2502.8 (RESET_N), U5405.4 (Y_OD), U5501.2 (A)
HOST_UART_TX: J3302.4, J4901.5, R3305.1
HOST_UART_TX_RAW: R3305.2, R3306.1, U5502.2 (A)
HOST_WDI: J3302.5, J4901.1, R2507.1, U2502.6 (WDI)
HOST_WDO_N: R2508.1, U2401.49 (PC9), U2502.7 (WDO_N), U2602.5 (1D), U5405.2 (A)
IO1V8: J4906.1, J4906.3, R1705.2, R1706.1, R3809.2, U3803.7 (IN-)
IO3V3: J4902.23, J4902.25, J4903.13, J4904.9, J4905.1, J4905.3, J4906.5, J4906.7, J4906.9, J4907.11, J4907.17, J4908.9, R1505.2, R1506.1, R3713.2, R6001.1, U3704.7 (IN-)
IO18_RAW: C1704.1, L1701.2, R1703.1, R1705.1, U1701.7 (FSW), U1701.14 (VOS), U3803.8 (IN+)
IO33_RAW: C1504.1, L1501.2, R1503.1, R1505.1, U1501.7 (FSW), U1501.14 (VOS), U3704.8 (IN+)
LINK_CLEAR_N: U5403.6 (CLR_N), U5404.4 (Y)
LINK_CWD: R5401.2, U5401.2 (CWD)
LINK_EDGE_H: U5402.4 (Y), U5403.1 (CLK)
LINK_READY_H: R5404.1, U2401.5 (PC15), U2602.13 (2D), U5403.5 (Q)
LINK_RESET_N: R5402.2, U5401.8 (RESET_N), U5404.1 (A)
LINK_WDO_N: R5403.2, U5401.7 (WDO_N), U5404.2 (B)
MATRIX_ARM_PULSE: R2607.1, U2401.14 (PC1), U2603.11 (2CLK)
MATRIX_INHIBIT_N: J2602.2, J4901.17, Q2602.3 (D), R2605.1, U2602.12 (2C)
MATRIX_KILL_GPIO: Q2602.1 (G), R2604.1, U2401.2 (PC12)
MATRIX_KILL_H: J2603.2, U2603.8 (2Q_N)
MATRIX_N_GATE: D2201.1 (K), Q2201.1 (G), Q2202.1 (G), Q2203.3 (D), R2202.1, R2204.1, U2201.3 (E)
MATRIX_N_SOURCE: D2201.2 (A), D2203.2 (A), Q2201.2 (S), Q2202.2 (S), Q2203.2 (S), R2202.2, U2202.3 (E)
MATRIX_OPTO_K: Q2104.3 (D), U2101.2 (K), U2201.2 (K), U2202.2 (K), U2203.2 (K)
MATRIX_PERMIT: J2603.1, Q2101.1 (G), Q2104.1 (G), Q2106.1 (G), R2106.1, R5316.1, U2401.48 (PC8), U3301.5 (2A), U5308.3 (2Y)
MATRIX_PERMIT_POWER: J3302.6, J4901.13, U3301.6 (2Y)
MATRIX_PERMIT_RAW: U2603.9 (2Q), U5308.5 (2A)
MATRIX_P_GATE: D2101.2 (A), Q2102.1 (G), Q2103.1 (G), Q2105.3 (D), R2101.1, R2102.1, R2103.1
MATRIX_P_SOURCE: D2101.1 (K), D2103.1 (K), Q2102.2 (S), Q2103.2 (S), Q2105.2 (S), R2102.2, U2101.4 (C)
MODE_CORE: R1207.2, R1208.1, U1201.18 (MODE)
MON_I_ANA5: C3806.1, R3808.1, U3901.17 (CH14)
MON_I_ANA6: C3606.1, R3608.1, U3901.4 (CH5)
MON_I_ANA33: C3812.1, R3816.1, U3901.16 (CH15)
MON_I_AON: C3506.1, R3508.1, U3901.8 (CH1)
MON_I_AUX18: C3706.1, R3708.1, U3901.22 (CH9)
MON_I_AUX25: C3709.1, R3712.1, U3901.21 (CH10)
MON_I_CORE: C3703.1, R3704.1, U3901.23 (CH8)
MON_I_DDR: C3805.1, R3807.1, U3901.19 (CH12)
MON_I_FPGA: C3603.1, R3604.1, U3901.5 (CH4)
MON_I_INPUT: C3503.1, R3504.2, U3901.9 (CH0)
MON_I_IO18: C3811.1, R3815.1, U3901.18 (CH13)
MON_I_IO33: C3712.1, R3716.1, U3901.20 (CH11)
MON_I_N15: C3403.1, D3401.3 (K1/A2), R3408.2, U3901.2 (CH7)
MON_I_P15: C3609.1, R3612.1, U3901.3 (CH6)
MON_I_SYS: C3512.1, R3516.1, U3901.6 (CH3)
MON_I_USB: C3509.1, R3512.1, U3901.7 (CH2)
MON_V_ANA5: C3802.1, R3803.1, R3804.1, U5600.5 (S2)
MON_V_ANA5_SAFE: D3802.3 (K1/A2), R5602.1, U3902.17 (CH14), U5600.6 (D2)
MON_V_ANA6: C3604.1, R3605.1, R3606.1, U2901.7 (IN2+), U5601.1 (S1)
MON_V_ANA6_SAFE: D3602.3 (K1/A2), R5604.1, U3902.4 (CH5), U5601.2 (D1)
MON_V_ANA33: C3808.1, R3811.1, R3812.1, U5600.1 (S1)
MON_V_ANA33_SAFE: D3804.3 (K1/A2), R5600.1, U3902.16 (CH15), U5600.2 (D1)
MON_V_AON: C3504.1, D3502.3 (K1/A2), R3505.1, R3506.1, U3902.8 (CH1)
MON_V_AUX18: C3704.1, R3705.1, R3706.1, U5601.5 (S2)
MON_V_AUX18_SAFE: D3702.3 (K1/A2), R5606.1, U3902.22 (CH9), U5601.6 (D2)
MON_V_AUX25: C3707.1, R3709.1, R3710.1, U5602.1 (S1)
MON_V_AUX25_SAFE: D3703.3 (K1/A2), R5608.1, U3902.21 (CH10), U5602.2 (D1)
MON_V_CORE: C3701.1, R3701.1, R3702.1, U5602.5 (S2)
MON_V_CORE_SAFE: D3701.3 (K1/A2), R5610.1, U3902.23 (CH8), U5602.6 (D2)
MON_V_DDR: C3801.1, R3801.1, R3802.1, U5603.1 (S1)
MON_V_DDR_SAFE: D3801.3 (K1/A2), R5612.1, U3902.19 (CH12), U5603.2 (D1)
MON_V_FPGA: C3601.1, R3601.1, R3602.1, U5603.5 (S2)
MON_V_FPGA_SAFE: D3601.3 (K1/A2), R5614.1, U3902.5 (CH4), U5603.6 (D2)
MON_V_INPUT: C3501.1, R3502.2, R3503.1, U5700.1 (S1)
MON_V_INPUT_SAFE: D3501.3 (K1/A2), R5700.1, U3902.9 (CH0), U5700.2 (D1)
MON_V_IO18: C3807.1, R3809.1, R3810.1, U5701.5 (S2)
MON_V_IO18_SAFE: D3803.3 (K1/A2), R5706.1, U3902.18 (CH13), U5701.6 (D2)
MON_V_IO33: C3710.1, R3713.1, R3714.1, U5700.5 (S2)
MON_V_IO33_SAFE: D3704.3 (K1/A2), R5702.1, U3902.20 (CH11), U5700.6 (D2)
MON_V_N15: C3404.1, D3402.3 (K1/A2), R3409.2, U2901.11 (IN4+), U3902.2 (CH7)
MON_V_P15: C3607.1, R3609.1, R3610.1, U2901.9 (IN3+), U5701.1 (S1)
MON_V_P15_SAFE: D3603.3 (K1/A2), R5704.1, U3902.3 (CH6), U5701.2 (D1)
MON_V_SYS: C3510.1, R3513.1, R3514.1, U5702.1 (S1)
MON_V_SYS_SAFE: D3504.3 (K1/A2), R5708.1, U3902.6 (CH3), U5702.2 (D1)
MON_V_USB: C3507.1, R3509.1, R3510.1, U2901.5 (IN1+), U5702.5 (S2)
MON_V_USB_SAFE: D3503.3 (K1/A2), R5710.1, U3902.7 (CH2), U5702.6 (D2)
MUX_A0: R4001.1, U2401.35 (PB15), U3901.10 (S0), U3902.10 (S0)
MUX_A1: R4002.1, U2401.36 (PA8), U3901.11 (S1), U3902.11 (S1)
MUX_A2: R4003.1, U2401.37 (PA9), U3901.14 (S2), U3902.14 (S2)
MUX_A3: R4004.1, U2401.38 (PC6), U3901.13 (S3), U3902.13 (S3)
MUX_DISABLE: R4007.1, U2401.39 (PC7), U3901.15 (DISABLE), U3902.15 (DISABLE)
MUX_I_COM: U3901.1 (COM), U4001.3 (IN+_A)
MUX_V_COM: U3902.1 (COM), U4001.5 (IN+_B)
N15: J4907.5, J4907.7, J4908.3, Q2201.3 (D), R1107.2, R1108.1, R3401.1, R3402.1
N15_RAW: C1106.2, C1107.2, C1108.2, C3402.1, D1101.2 (A), R1107.1, R3403.1, U1102.5 (-VOUT), U3401.4 (V-)
N15_REMOTE_EN: Q1103.3 (D), U1102.6 (REMOTE)
unnamed: C1205.1, L1201.1, U1201.6 (SW), U1201.7 (SW)
unnamed: C2101.1, R2103.2
unnamed: C2201.1, R2204.2
unnamed: D101.1 (K), D102.2 (A), R101.1
unnamed: D201.1 (K), D202.2 (A), Q201.3 (D), R201.2
unnamed: D203.1 (K), D204.2 (A), R202.1
unnamed: D302.2 (A), R306.2
unnamed: D401.2 (A), R402.1
unnamed: D501.1 (K), R504.2
unnamed: D601.1 (K), R605.2
unnamed: D701.2 (A), R706.2
unnamed: D801.2 (A), R806.2
unnamed: D901.1 (K), R905.2
unnamed: D1001.1 (K), R1005.1
unnamed: D2103.2 (A), Q2105.1 (G), R2107.1, U2101.3 (E)
unnamed: C2103.1, D2104.1 (K), Q2106.3 (D), Q2107.1 (G), R2108.2
unnamed: D2203.1 (K), Q2203.1 (G), R2207.1, U2202.4 (C)
unnamed: C2203.1, D2204.2 (A), Q2204.1 (G), R2209.2, U2203.3 (E)
unnamed: J2501.2, R2501.1, U2501.3 (MR_N)
unnamed: J2502.2, R2506.1, U2502.3 (MR_N)
unnamed: J2601.2, Q2601.3 (D), R2602.1, U2601.12 (2C)
unnamed: J3301.3, R3301.2
unnamed: J3301.4, R3302.2
unnamed: JP301.1 (A), U301.13 (SHDN_N)
unnamed: L1301.1, U1301.1 (SW), U1301.2 (SW), U1301.3 (SW)
unnamed: L1401.1, U1401.1 (SW), U1401.2 (SW), U1401.3 (SW)
unnamed: L1501.1, U1501.1 (SW), U1501.2 (SW), U1501.3 (SW)
unnamed: L1601.1, U1601.1 (SW), U1601.2 (SW), U1601.3 (SW)
unnamed: L1701.1, U1701.1 (SW), U1701.2 (SW), U1701.3 (SW)
unnamed: Q201.1 (G), R203.2, R204.1
unnamed: C303.1, Q301.2 (D), U301.1 (IN), U301.2 (IN), U301.3 (IN)
unnamed: Q301.1 (G), Q302.3 (D), U301.4 (B_GATE)
unnamed: Q302.1 (G), U301.5 (DRV)
unnamed: Q2101.3 (D), R2101.2
unnamed: Q2107.3 (D), R2109.2, R2110.2
unnamed: Q2204.3 (D), R2210.2, R2211.2
unnamed: R303.2, R304.1
unnamed: R309.1, R310.2
unnamed: R403.1, R404.2
unnamed: R2301.2, R2302.1, R2303.1
unnamed: R3501.1, R3502.1
unnamed: R305.1, U301.11 (ILIM)
unnamed: R308.1, R309.2, U301.16 (PGTH)
unnamed: C304.1, U301.10 (dVdT)
unnamed: C1205.2, U1201.1 (BOOT)
unnamed: C1203.1, U1201.14 (SS)
unnamed: C1301.1, U1301.9 (SS/TR)
unnamed: C1401.1, U1401.9 (SS/TR)
unnamed: C1501.1, U1501.9 (SS/TR)
unnamed: C1601.1, U1601.9 (SS/TR)
unnamed: C1701.1, U1701.9 (SS/TR)
unnamed: C1902.1, U1901.8 (NR/SS)
unnamed: C2002.1, U2001.8 (NR/SS)
unnamed: R2105.2, U2101.1 (A)
unnamed: R2201.2, U2201.1 (A)
unnamed: R2203.2, U2201.4 (C)
unnamed: R2206.2, U2202.1 (A)
unnamed: R2208.2, U2203.1 (A)
unnamed: C2901.1, R2901.2, R2905.1, U2901.4 (IN1-)
unnamed: C2902.1, R2902.2, R2906.1, U2901.6 (IN2-)
unnamed: C2903.1, R2903.2, R2907.1, U2901.8 (IN3-)
unnamed: C2904.1, R2904.2, R2908.1, U2901.10 (IN4-)
unnamed: C3201.1, R3201.2, R3202.1, U3201.5 (IN1+)
unnamed: R3401.2, R3404.1, U3401.3 (IN+_A)
unnamed: R3403.2, R3405.2, U3401.2 (IN-_A)
unnamed: R3402.2, R3406.2, U3401.6 (IN-_B)
unnamed: R3405.1, R3407.1, R3408.1, U3401.1 (OUT_A)
unnamed: R3406.1, R3409.1, U3401.7 (OUT_B)
unnamed: R3504.1, U3501.1 (OUT)
unnamed: R3507.1, U3502.3 (LIMIT)
unnamed: R3508.2, U3502.2 (OUT)
unnamed: R3511.1, U3503.3 (LIMIT)
unnamed: R3512.2, U3503.2 (OUT)
unnamed: R3515.1, U3504.3 (LIMIT)
unnamed: R3516.2, U3504.2 (OUT)
unnamed: R3603.1, U3601.3 (LIMIT)
unnamed: R3604.2, U3601.2 (OUT)
unnamed: R3607.1, U3602.3 (LIMIT)
unnamed: R3608.2, U3602.2 (OUT)
unnamed: R3611.1, U3603.3 (LIMIT)
unnamed: R3612.2, U3603.2 (OUT)
unnamed: R3703.1, U3701.3 (LIMIT)
unnamed: R3704.2, U3701.2 (OUT)
unnamed: R3707.1, U3702.3 (LIMIT)
unnamed: R3708.2, U3702.2 (OUT)
unnamed: R3711.1, U3703.3 (LIMIT)
unnamed: R3712.2, U3703.2 (OUT)
unnamed: R3715.1, U3704.3 (LIMIT)
unnamed: R3716.2, U3704.2 (OUT)
unnamed: R3805.1, U3801.3 (LIMIT)
unnamed: R3807.2, U3801.2 (OUT)
unnamed: R3806.1, U3802.3 (LIMIT)
unnamed: R3808.2, U3802.2 (OUT)
unnamed: R3813.1, U3803.3 (LIMIT)
unnamed: R3815.2, U3803.2 (OUT)
unnamed: R3814.1, U3804.3 (LIMIT)
unnamed: R3816.2, U3804.2 (OUT)
unnamed: R4005.1, U4001.1 (OUT_A), U4001.2 (IN-_A)
unnamed: R4006.1, U4001.6 (IN-_B), U4001.7 (OUT_B)
OC_I_N15: D3403.3 (K1/A2), R3407.2, U3201.4 (IN1-)
OC_OK_N: R3203.2, R4008.1, U2401.44 (PA12), U2601.10 (2B), U3201.2 (OUT1), U3502.6 (~ALERT), U3503.6 (~ALERT), U3504.6 (~ALERT), U3601.6 (~ALERT), U3602.6 (~ALERT), U3603.6 (~ALERT), U3701.6 (~ALERT), U3702.6 (~ALERT), U3703.6 (~ALERT), U3704.6 (~ALERT), U3801.6 (~ALERT), U3802.6 (~ALERT), U3803.6 (~ALERT), U3804.6 (~ALERT)
P15: J4907.1, J4907.3, J4908.1, Q2102.3 (D), R1004.2, R1005.2, R1006.1, R3609.2, U3603.7 (IN-)
P15_RAW: C1004.1, C1005.1, C1006.1, C1007.1, C1010.1, L1001.2, R1002.1, R1004.1, U3603.8 (IN+)
P15_SW: C1001.2, L1001.1, U1001.8 (SW)
P15_VCC: C1009.1, U1001.6 (VCC)
PGR_ANA5: R1902.1, U1901.5 (PG), U2401.63 (PB9), U3017.10 (2B)
PGR_ANA33: R2002.1, U2001.5 (PG), U2401.64 (PC10), U3017.12 (2C)
PGR_AUX18: R1302.1, U1301.4 (PG), U2401.57 (PB3), U3001.13 (2D), U6000.3 (B)
PGR_AUX25: R1402.1, U1401.4 (PG), U2401.58 (PB4), U3017.1 (1A)
PGR_CORE: R1202.1, U1201.16 (PGOOD), U2401.56 (PD6), U3001.12 (2C)
PGR_DDR: R1602.1, U1601.4 (PG), U2401.60 (PB6), U3017.4 (1C)
PGR_IO18: R1702.1, U1701.4 (PG), U2401.61 (PB7), U3017.5 (1D)
PGR_IO33: R1502.1, U1501.4 (PG), U2401.59 (PB5), U3017.2 (1B)
PGR_VTT: R1804.1, U1801.9 (PGOOD), U2401.62 (PB8), U3017.9 (2A)
PG_ANA: R2910.1, U2401.53 (PD3), U2901.1 (OUT2), U3001.5 (1D)
PG_FPGA: R801.2, U801.16 (PGOOD), U2401.52 (PD2), U3001.4 (1C)
PG_INPUT: R307.1, U301.17 (PGOOD), U2401.42 (PA10), U2601.4 (1C)
PG_N15: R2912.1, U2401.55 (PD5), U2901.13 (OUT4), U3001.10 (2B)
PG_P15: R2911.1, U2401.54 (PD4), U2901.14 (OUT3), U3001.9 (2A)
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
